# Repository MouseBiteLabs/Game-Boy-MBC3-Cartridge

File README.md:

# Game Boy MBC3 Cartridge

This is my design of a flashable MBC3-based cartridge for the Game Boy. The MBC3 mapper improves a lot over the MBC1, and includes a real-time clock for everyone's favorite battery-sucking game.... Mary Kate and Ashley Pocket Planner! Oh, and Pokemon.

This circuit board should cover most, if not all, MBC3 games. The features are as follows:

- Able to make games up to 2 MB in size, that use up to 256 Kbit of RAM
- Compatibility with all four of the popular Game Boy battery management ICs - MM1026, MM1134, BA6129, and BA6735
- The option to add battery backup to the cartridge *without* the need of the original battery management ICs
- Fully compatible with the <a href="https://www.gbxcart.com/">GBxCart RW</a> so you can transfer games and save files to and from the board
- 

All gerbers and source files can be found in this repo, as this project is fully open source. Technical documentation of the board can be found in the Technical folder.

## Important Things Before You Start

1) To use this board, you need to have an original Game Boy game that uses an MBC3 mapper chip. <a href="https://catskull.net/gb-rom-database/">You can find a list of games and their mappers here</a>. Use the search function. Please note the RAM is in bytes, not bits. Since SRAM in this repo is defined in bits, you need to convert by multiplying the number of bytes by 8.
2) You will need to remove the MBC3 from your donor cartridge for use on this board. This will require a hot air rework station or a hot plate. There's a list below of other parts you can re-use from the donor cartridge.
3) When soldering parts on, it's a good idea to put kapton tape or otherwise cover the bottom cartridge edge. You do not want to get solder on the cartridge contacts.
4) I am not responsible for any damage you do to your self or your property. Attempt this project at your own risk.
5) I do not guarantee design compatibility. You may encounter issues with certain games. There is also a chance I have made an error in the design or the BOM - if this is the case, I will do everything I can to address the problem as quickly as possible.
6) If you are using this board to make games other than for personal use, you must have permission from the originator to use and distribute any ROM images or other related material. You are responsible for making sure you adhere to any license requirements.

DO NOT use my circuit boards for profiting from stolen work - this especially includes homebrew content, ROM hacks, and using fan-made labels without permission from the originator. **Support original creators!**

## Board Characteristics and Order Information

The zipped folder contains all the gerber files for this board. The following options **must** be chosen when ordering boards for yourself.

- Thickness: 0.8mm
- Surface Finish: ENIG
- Gold Fingers: Yes, 30° chamfer

**Add this note to orders:** "The milling.gbr layer indicates where an unplated slot should be added to the board. Please add an unplated slot as indicated."

**I sell this blank circuit board on Etsy, so you don't have to buy a bunch of multiples if you don't want to.** (Click the banner!)

You can use the zipped folder at any board fabricator you like. You may also buy the board from PCBWay using this link (disclosure: I receive 10% of the sale value to go twoards future PCB orders of my own):

<a href="https://oshpark.com/shared_projects/6rPI4Bk8">The board is also listed on OSH Park as well.</a> **Be sure to get them in 0.8mm thickness if you order from here.**

## Required Equipment

The EEPROMs on the board needs to be programmed somehow. I recommend using the GBxCart, as mentioned. These boards are fully compatible with it, and it makes reflashing games extremely easy using <a href="https://github.com/lesserkuma/FlashGBX">lesserkuma's FlashGBX software</a>.

Alternatively, you can buy an EEPROM programmer with a TSOP adapter. The downside to this method is that you have to desolder the chip every time you want to program it. The <a href="https://flashcatusb.com/">FlashcatUSB</a> is one popular option in retro spaces.

## Battery Safety

When assembling a board, I recommend populating all the parts *except* the battery, and getting it to run initially without it. This is to make it easier to fix any solder connections that might need fixing, without having to worry about getting the battery hot. And if you need to rework anything near the battery after you've put it on the board, be safe and remove it before putting a hot soldering iron next to it.

And this should go without saying, but if you're assembling these boards with a hot plate or hot air, *do not* solder the battery on this way. You should use an iron, and keep heat off of the battery as much as possible. 

(Also check polarity!)

## Board Configurations

The board comes with five sets of jumper pads for solder bridges. SJ3, SJ5, and SJ6 require you to solder bridge the middle pad either to the left or right pads. SJ1 and SJ4 are configured by either leaving them alone or bridging them with solder. Here are the situations where you need to add solder bridges.

### Making Games Without SRAM or Battery (SJ1 and SJ4)

Solder bridge SJ1 and SJ4 if your game does not use any SRAM or battery. I don't believe there were ever any MBC3 games made *without* SRAM, but if you wanted to... remove it for some reason, you can.

### MBC3 Type Select (SJ3)

The MBC3 chip you use from the donor cartridge can be one of a few different types:

- If your MBC3 doesn't have a revision letter on it (it just says "MBC3" on it) then bridge the middle pad of SJ3 to the left. (You will also need to populate Q1!)
  - If you're using a revision-less MBC3, and are making a game that requires a battery, you should use a donor MM1026, MM1134, BA6129, or BA6735 battery management IC instead of the replacement TPS3613.
- If your MBC3 *does* have a revision letter, such as MBC3A or MBC3B, then bridge the middle pad of SJ3 to the right.

*[Images of MBC3 chips from <a href="https://gbhwdb.gekkio.fi/cartridges/mbc3.html">Game Boy Hardware Database</a>.]*

### RAM Size Selection (SJ5 and SJ6, or SW1)

These jumpers are located underneath the MBC3 chip, and labeled "64K" and "256K". Solder them to configure the amount of RAM your cart uses. You must configure these pads for every game you make, unless you do not need RAM. <a href="https://catskull.net/gb-rom-database/">You can find a list of games here with their respective RAM sizes.</a>

- If the game you're making uses 256 Kbit of RAM, then solder the middle pads of the two jumper sets to the right pads.
- If the game you're making uses 64 Kbit of RAM, then solder the middle pads of the two jumper sets to the left pads.
- SJ5 and SJ6 must be soldered in the same direction.
- The footprint of these selection pads should allow for a DPDT switch, part number CAS-220A1, to be placed on these pads instead of having to bridge the pads with solder.

Note that you can make games that only require 64 Kbit of RAM and still use a 256 Kbit SRAM chip. You still need to configure the jumpers to the 64 Kbit setting, though.

### Games Without a Real-Time Clock

If your game does *not* use the RTC function with the crystal X1, then you need to bridge the pads of Z1 (which is called C3 on v1.3 and earlier).

## Test Points and Final Checkout

On the back of the board are five test points. Here's where they are connected:

- TP1: SRAM supply voltage
- TP2: Battery voltage (after R1)
- TP3: Battery voltage (positive terminal of battery)
- TP4: Ground
- TP5: VCC input voltage

After you assemble your game, you should measure the current out of the battery. But first, you should program it with the GBxCart, or if you programmed the EEPROM separately, put it into a Game Boy and cycle power once. Then, flip the PCB upside down on a non-conductive surface (not your leg), and set your multimeter in DC millivolts (or volts). Put the positive probe on TP3 and the negative probe on TP2. If you used a 10kΩ for R1, as indicated in the BOM, you should read a voltage in the single or tens of millivolts for non-RTC games, or up to 40 mV for games using a real-time clock. If you have something much higher, especially voltages above 40mV, then you likely have an issue or short circuit on the board somewhere.

**Note: You need to power up the game at least once before battery currents will make sense - the battery management ICs can start up in an unknown state before applying main power to the board.**

To estimate battery life, see <a href="https://github.com/MouseBiteLabs/Game-Boy-MBC3-Cartridge/tree/main/Technical#estimating-battery-life">this section in the Technical Design Document</a>, or for more in-depth analysis, <a href="https://hackaday.io/project/11864-tritiled/log/72554-determining-maximum-runtime-176-to-202-years-cr2032">this Hackaday post</a>.

### Current Draw Measurements

The revision of MBC3 chip you are using will influence the current draw out of the battery when the game is off, and thus how long your battery life will last. Using the real-time clock function on the MBC3 will draw more current than if you do not.

For the test set up, I am replacing the battery with a regulated DC power supply set for 3 VDC for consistency, on a cart board with an MM1134 chip for U4, and brand new AS6C62256 SRAM. The "no RTC" measurements have Z1 (or C3) shorted, and the "with RTC" measurements have R2, C2, Z1, and X1 populated. I am using a Fluke 117 Multimeter in DC mV mode for measurements.

| Rev   | P/N      | Current draw (without RTC) | Battery Life Estimate (no RTC, CR2025) | Current draw (with RTC) | Battery Life Estimate (RTC, CR2025)  | Battery Life Estimate (RTC, CR2032) |
| ----- | -------- | -------------------------- | -------------------------------------- | ----------------------- | ------------------------------------ | ----------------------------------- |
| MBC3  | LR385364 |          0.2 uA            |               >50 years                |            1.8 uA       |               10 years               |            14 years                 |
| MBC3  | BU3631K  |          0.6 uA            |                31 years                |            1.6 uA       |               12 years               |            16 years                 |
| MBC3  | P-1      |          0.4 uA            |                47 years                |            3.8 uA       |               5 years                |             7 years                 |
| MBC3A | LR38536B |          0.2 uA            |               >50 years                |            1.5 uA       |               13 years               |            18 years                 |
| MBC3A | BU3632K  |          0.5 uA            |                37 years                |            1.5 uA       |               13 years               |            18 years                 |
| MBC3A | P-2      |          0.5 uA            |                37 years                |            3.9 uA       |               5 years                |            7 years                  |
| MBC3B | BU3634K  |          0.6 uA            |                31 years                |            1.5 uA       |               13 years               |            18 years                 |
| MBC3B | P-2      |          0.4 uA            |                47 years                |            3.7 uA       |               5 years                |            7 years                  |

*Note: The SRAM I used, AS6C62256, drew 0.05 uA by itself for these tests. Your current draw may vary depending on the SRAM you are using.*

### Why not FRAM?

This board is only suitable for using SRAM. One downside to SRAM, if you haven't figured it out yet, is that you need a battery to keep the SRAM powered on even when the game is turned off. So eventually the battery will die, and your save data is lost. Some people have used FRAM, or Ferroelectric RAM, to keep save data around even after the battery dies (specifically, the popular part that's used for FRAM carts is the FM18W08). But, using this FRAM chip has a handful of downsides, and the benefit of keeping save data after the battery dies *in my opinion* does not outweigh the cons, which are as follows:

1) Quality, new stock, 5V tolerant FRAM is expensive ($12+ per part).
2) Cheaper FRAM chips from eBay or Aliexpress are notoriously flaky (anecdotally, ~50% success rate).
3) FRAM memory access requires different chip select timing than SRAM, and the Game Boy expects SRAM, so it is not natively compatible with FRAM carts. The Gameboy Color specifically cannot (easily) be made to properly access FM18W08 chip. You *can* use an OR gate and add the CLK on the cart edge to try to achieve the necessary timing, but it only works (properly) for DMG/MGB/SGB, not the GBC. It usually *works* in practice for GBC, but it's technically a datasheet violation and can potentially cause issues in edge cases. <a href="https://github.com/Gekkio">(Thanks to gekkio for pointing this out!)</a>

Brand new SRAM chips are ~$3, and having the SRAM footprint also allows you to use SRAM from an original cart if desired. And other than the scenario where you are making a game with a real-time clock and are using an inefficient MBC3 variant (P-1 or P-2), you can easily get more than a decade of battery life. You're already assembling this cartridge; you can dump the save and replace the battery!

Note that this isn't to throw shade at any FRAM-based carts, but for me personally, it's more trouble than it's worth. If you just *need* FRAM, you can find other cart designs out there that have it, <a href="https://retrogamerepairshop.com/products/game-boy-2mb-32kb-fram-mbc3-with-rtc-flash-cartridge-by-hdr?variant=40144623927468">like this one!</a>

## Board Fitment

The shape of this board was originally meant to mimic original Game Boy circuit boards as closely as possible (v1.3 and earlier). Unfortunately, when placed in some aftermarket Game Boy cartridge shells (like those from Cloud Game Store), the circuit board has a lot of freedom to rotate around the main screw hole in the bottom-middle of the cartridge. This can cause misalignment when you put it in a Game Boy, which can cause a game to either not load properly (garbled Game Boy logo) or shut off the Game Boy because of a short circuit. This isn't *dangerous* or anything, just annoying.

In order to make the boards fit nicer in any kind of shell, for v1.4 I added extended tabs of circuit board material to the edges of the cartridges to keep it from rotating too much in shells, which was suggested to me by <a href="https://github.com/orangeglo">orangeglo</a>! (Thanks!)

If you're having trouble fitting the circuit board into a shell, because the tabs interfere with the cart edges, you can safely sand or trim them down as there is no copper within the tabs themselves. The only shell that appears to require any kind of trimming are Kitsch-Bent shells.

## Bill of Materials (BOM)

Your parts list will vary depending on the game you are trying to make, and what chips you have for the battery management (if any). **You cannot use both U4 and U5 - you must choose one or the other.** U4 comes from a donor cartridge, and U5 is a readily available aftermarket option.

Please carefully review the parts you need for the board you are trying to make. Do not add any parts to your build that don't appear in the column for the game you are making. This means you *cannot* populate every component on the board at the same time.

**NOTE: If you are *not* using the RTC function of the MBC3, you need to bridge the pads of Z1 (or C3) with solder.**

| Reference Designators | Value/Part Number              | Package          | Description        | No save carts | Save carts with U4 | Save carts without U4 | Source                                           |
| --------------------- | ------------------------------ | ---------------- | ------------------ | ------------- | ------------------ | --------------------- | ------------------------------------------------ |
| B1                    | CR2032, CR2025, CR2016         | CR2032           | Backup Battery     |               | x                  | x                     | [https://mou.sr/3SeAzfT](https://mou.sr/3SeAzfT) |
| C1                    | 0.1uF                          | 0603             | Capacitor (MLCC)   | x             | x                  | x                     | [https://mou.sr/3ENc15O](https://mou.sr/3ENc15O) |
| C2                    | 15pF                           | 0603             | Capacitor (MLCC)   |               | If using RTC       | If using RTC          | https://mou.sr/3PPorjO                           |
| Z1 (or C3)            | 15pF                           | 0603             | Capacitor (MLCC)   |               | If using RTC       | If using RTC          | https://mou.sr/3PPorjO                           |
| C4                    | 0.1uF                          | 0603             | Capacitor (MLCC)   |               | x                  |                       | [https://mou.sr/3ENc15O](https://mou.sr/3ENc15O) |
| C5                    | 0.1uF                          | 0603             | Capacitor (MLCC)   |               | x                  | x                     | [https://mou.sr/3ENc15O](https://mou.sr/3ENc15O) |
| C6                    | 10uF                           | 0603             | Capacitor (MLCC)   |               | x                  | x                     | [https://mou.sr/3mZtSkF](https://mou.sr/3mZtSkF) |
| C7                    | 0.1uF                          | 0603             | Capacitor (MLCC)   | x             | x                  | x                     | [https://mou.sr/3ENc15O](https://mou.sr/3ENc15O) |
| C8                    | 0.1uF                          | 0603             | Capacitor (MLCC)   |               |                    | x                     | [https://mou.sr/3ENc15O](https://mou.sr/3ENc15O) |
| Q1                    | 2N7002                         | SOT-23           | N-Channel FET      |               | If MBC3 no rev     | x                     | [https://mou.sr/3rgfh6J](https://mou.sr/3rgfh6J) |
| R1                    | 10k                            | 0603             | Resistor           |               | x                  | x                     | [https://mou.sr/3riR7IH](https://mou.sr/3riR7IH) |
| R2                    | 330k                           | 0603             | Resistor           |               | If using RTC       | If using RTC          | [https://mou.sr/3PZ2pvj](https://mou.sr/3PZ2pvj) |
| R8                    | 10k                            | 0603             | Resistor           | x             | x                  | x                     | https://mou.sr/3riR7IH                           |
| R9                    | 130k                           | 0603             | Resistor           |               |                    | x                     | [https://mou.sr/3MjXliy](https://mou.sr/3MjXliy) |
| R10                   | 49.9k                          | 0603             | Resistor           |               |                    | x                     | https://mou.sr/3Q3NRZO                           |
| U1                    | 29F016, 29F032, 29F033         | TSOP-48, TSOP-40 | Flash EEPROM       | x             | x                  | x                     | AliExpress or eBay                               |
| U2                    | MBC3                           | QFP-32           | MBC3 Mapper        | x             | x                  | x                     | Donor MBC3 Game Boy cartridge                    |
| U3                    | AS6C6264, AS6C62256            | SOP-28           | SRAM               |               | x                  | x                     | [https://mou.sr/450klcY](https://mou.sr/450klcY) |
| U4                    | MM1026, MM1134, BA6129, BA6735 | SOIC-8           | Battery Management |               | x                  |                       | Donor Game Boy cartridge                         |
| U5                    | TPS3613                        | MSOP-10          | Battery Management |               |                    | x                     | [https://mou.sr/45Ir2kh](https://mou.sr/45Ir2kh) |
| X1                    | 32.768 kHz                     | Radial           | Crystal Oscillator |               | If using RTC       | If using RTC          | https://mou.sr/3ZteKuy                           |

*Note that C9 - C11 footprints are only included on the board for strange edge cases that may require them sometime in the future; do not populate! See the technical design document for more information.*

### Usable Donor Cartridge Parts

You can use a few parts from the donor cart on the new board to save some money. Note that you will generally get better reliability with new parts as opposed to old ones. For example: I have seen failed RAM chips from donors in the past.

1) **C1/Z1, C2, R2, X1: RTC Components** - You can move over these parts if you're using the real-time clock function. The two capacitors are the same value, so they are interchangeable. On games that *don't* use the RTC, you can't move "Z1" over, because it's a resistor on those boards. Also be careful that on my board, the RTC capacitors are designated as "Z1" (or "C3") and "C2" - don't accidentally move the wrong capacitors over from the donor board to these spots!
2) **U2: MBC3** - This one is required
3) **U3: SRAM** - You can use this part *only if* the game you're making uses the same or less amount of RAM that the donor cartridge does
4) **U4: Battery Management IC** - Using this is probably preferred over the TPS3613 because it'll save you money and parts to put on

You could probably transfer over most of the 0.1uF capacitors but they're pretty cheap anyway, so I generally just recommend buying new resistors and capacitors.

### Capacitors C9 to C11

If you want to experiment with the capacitors C9 to C11, see this info below. **Be aware that adding these components in some of my tests actually ***stopped*** games from working, so again, assume that if you have a problem it lies elsewhere first, because it almost certainly does.**
- C9 is a capacitor connected nearby the SRAM's /WE pin to GND. These were populated on some cartridges, and I believe have a value of approximately 1 nF (0.001 uF) based on measurements from an MBC1 board that used it.
- C10 is a capacitor connected from the cart edge /RESET pin to GND. A spot for this capacitor was included on some MBC1 carts, but I cannot locate an instance of it actually being used when looking through the gbhwdb. It does not appear on *any* MBC3 boards. I don't actually know what value this capacitor would need to be, so I am guessing 1 nF.
- C11 is a capacitor that I have added that was not used on any original Game Boy board. It connects to the SRAM's /CE pin, bypassing to GND. I have added this in the event incompatibilities arise with newer SRAM chips that have much faster speeds than older SRAM chips. This was a problem I encountered on some of my NES cartridges, so this is here just in case, but I have not found an instance where it's required.

## Things to Remember

- The footprint for the EEPROM is specifically for 29F016 - it has 48 pins. However, 29F032 and 29F033 are only 40 pin devices. They still work fine on the board though - place them in the center of the footprint, and leave the outer two pins on each corner empty
- The 29F016, 29F032, and 29F033 have been known to occasionally be defective upon arrival. They're either used, or new old stock, and usually only available from AliExpress.
- The footprint for the battery can fit a CR2032, CR2025, or CR2016 with solder tabs. The only difference is the mAh capacity (larger number = longer life). If you get Panasonic tabbed batteries, you may have to trim the battery tabs to make them fit on the footprint.
  - For untabbed coin cells, you can find battery retainer adapters online, <a href="https://retrogamerepairshop.com/products/hdr-game-boy-game-battery-retainer?variant=40511013290156">like this one,</a> but only for board revision v1.4. It will not fit on earlier revisions.
- For battery management, use either U4 *or* U5 and supporting components. **Do not** use U4 and U5 simultaneously on one board. They will interfere with each other.
- Generally, ROM sizes are conveyed in terms of kilo**bytes** and mega**bytes** (KB, MB). RAM size is usually conveyed in terms of kilo**bits** or mega**bits** (Kbit, Mbit). You can convert Kbit and Mbit to KB and MB by dividing Kbit or Mbit by 8. For example, 256 Kbit = 32 KB.
- You only need to provide ROM and RAM chips that have at least *or greater* the size of the game you are trying to make. That means you can use a 256 Kbit SRAM chip for a game that only requires 64 Kbit of RAM!

## Labels

If you want a Bucket Mouse branded label for your cartridge, look no further than <a href="https://krizdingus.com/mousebitelabs/">krizdingus's designs</a>. Special thanks to Kris for designing these, they look awesome! (If you are going to order/print these, use the high-res images hosted on his website, and *keep the labels for personal or non-commercial use only.*)

## Revision History

### v1.4
- Changed "C3" to "Z1"
- Reduced cart edge by 0.1 mm for better fitment
- Adjusted battery placement to support more battery holders
- Added tabs on the board edges to allow the circuit board to fit better in aftermarket cartridge shells

### v1.3
- Extended cart edge down by 0.25 mm for better fitment
- Added OSHW logo and "SUPPORT ORIGINAL CREATORS!"

### v1.2
- Replace non-donor battery management circuitry with a TPS3613-based circuit for smaller BOM and easier routing

### v1.1
- Moved all parts on the top down to allow for compatibility with DMG-style shells
- Rotated battery for more space
- Widen SRAM footprint for easier soldering
- Renamed some reference designators for consistency between designs
- Changed silkscreen for clarity

### v1.0
- Prototype revision

## Resources and Acknowledgements

- <a href="http://www.devrs.com/gb/files/hardware.html">Jeff Frohwein's GameBoy Tech Page</a>
- <a href="https://gbhwdb.gekkio.fi/">Game Boy Hardware Database</a>
- <a href="https://catskull.net/gb-rom-database/">Nintendo Gameboy Game List</a>
- <a href="https://www.gbxcart.com/">insideGadgets discord server for GBxCart RW compatibility requirements</a>
- <a href="https://github.com/lesserkuma/FlashGBX">Lesserkuma's FlashGBX software</a>
- <a href="https://www.alldatasheet.com/datasheet-pdf/pdf/99104/MITSUBISHI/MM1026.html">System Reset IC Datasheet</a>
- <a href="https://www.ti.com/lit/ds/symlink/tps3613-01.pdf?HQS=dis-mous-null-mousermode-dsf-pf-null-wwe&ts=1698238885366&ref_url=https%253A%252F%252Feu.mouser.com%252F">TPS3613 Datasheet</a>
- Board outline modified from <a href="https://tinkerer.us/projects/homebrew-gameboy-cartridge.html">Dillon Nichols's Homebrew Gameboy Cartridge project</a>
- Thanks to <a href="https://github.com/orangeglo">orangeglo</a> for his suggestion of adding spacers around the board edge for better fitment in aftermarket cartridges
- Some components from <a href="https://github.com/adafruit/Adafruit-Eagle-Library">Adafruit's Eagle parts library</a>
- Some components from <a href="https://www.snapeda.com/">SnapMagic</a>
- Thank you to <a href="https://github.com/Gekkio">gekkio</a> for their deep Game Boy knowledge resources, and for collaboration in demystifying some of the design choices on Game Boy cartridges
- Thanks to the awesome members of the <a href="https://moddedgameboy.club/">Modded Gameboy Club</a> for their feedback and support during the entire project development

## License

<br />This work is licensed under a <a rel="license" href="http://creativecommons.org/licenses/by-sa/4.0/">Creative Commons Attribution-ShareAlike 4.0 International License</a>. You are able to copy and redistribute the material in any medium or format, as well as remix, transform, or build upon the material for any purpose (even commercial) - but you **must** give appropriate credit, provide a link to the license, and indicate if any changes were made.

©MouseBiteLabs 2023

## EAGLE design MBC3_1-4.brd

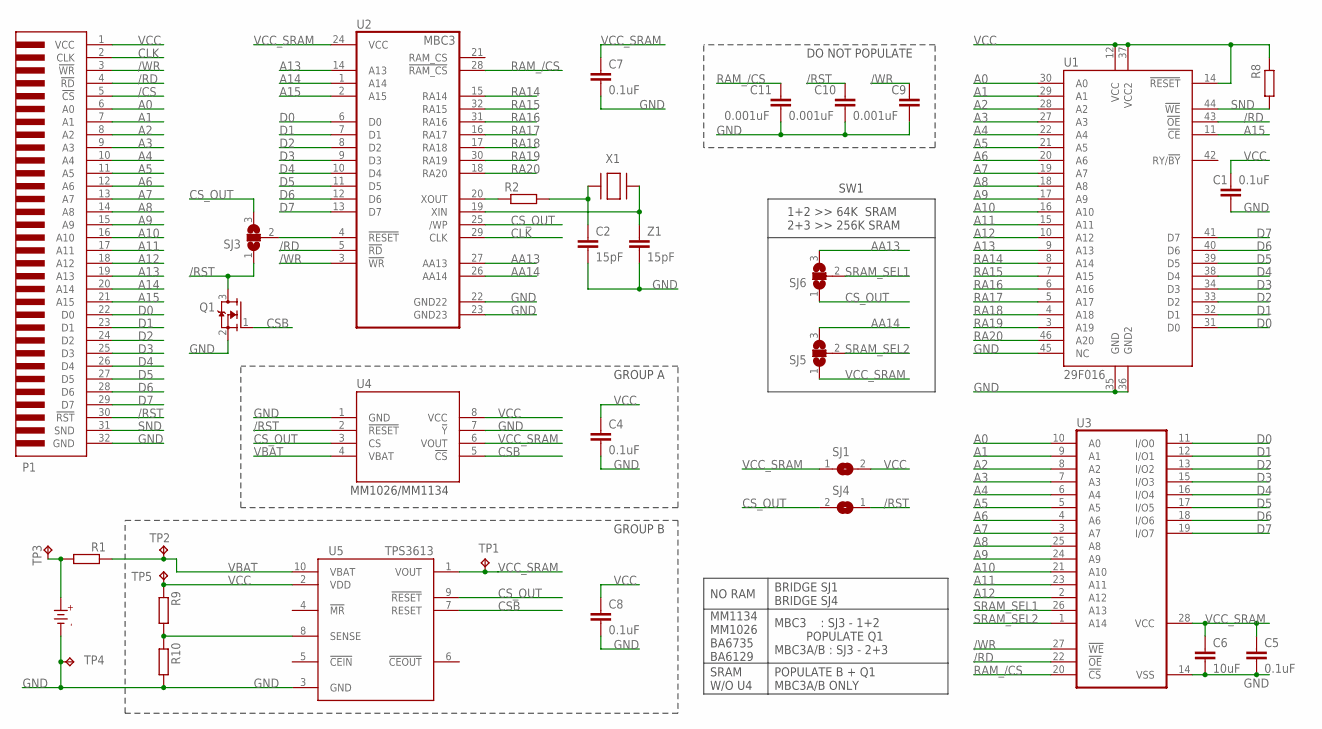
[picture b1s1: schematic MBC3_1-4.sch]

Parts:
B1: CR2025
C1, C4, C5, C7, C8: 0.1uF; C0603
C2: 15pF; C0603
C6: 10uF; C0603
C9, C10, C11: 0.001uF; C0603
P1: GBC_CARTTAB; GBC_CART_TABBED
Q1: 2N7002; SOT23
R1, R2, R8, R9, R10: RR0603; R0603
SJ1, SJ4: SJ
SJ3, SJ5, SJ6: SJ2W; SJ_2
TP1, TP2, TP3, TP4, TP5: TPB1,27; B1,27
U1: 29F016; TSOP-48
U2: MBC3; QFP-32
U3: 62256_SRAM; SOP-28L
U4: MM1134; SOIC-8
U5: TPS3613; MSOP-10
X1: XTAL-3.2X1.5; XTAL3215
Z1: 15pF; C0603

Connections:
/CS: P1.5 (!CS)
/RD: P1.4 (!RD), U1.43 (!OE), U2.5 (!RD), U3.22 (!OE)
/RST: C10.1, P1.30 (!RST), Q1.3 (D), SJ3.1, SJ4.1, U4.2 (!RESET)
/WR: C9.1, P1.3 (!WR), U2.3 (!WR), U3.27 (!WE)
A0: P1.6 (A0), U1.30 (A0), U3.10 (A0)
A1: P1.7 (A1), U1.29 (A1), U3.9 (A1)
A2: P1.8 (A2), U1.28 (A2), U3.8 (A2)
A3: P1.9 (A3), U1.27 (A3), U3.7 (A3)
A4: P1.10 (A4), U1.22 (A4), U3.6 (A4)
A5: P1.11 (A5), U1.21 (A5), U3.5 (A5)
A6: P1.12 (A6), U1.20 (A6), U3.4 (A6)
A7: P1.13 (A7), U1.19 (A7), U3.3 (A7)
A8: P1.14 (A8), U1.18 (A8), U3.25 (A8)
A9: P1.15 (A9), U1.17 (A9), U3.24 (A9)
A10: P1.16 (A10), U1.16 (A10), U3.21 (A10)
A11: P1.17 (A11), U1.15 (A11), U3.23 (A11)
A12: P1.18 (A12), U1.10 (A12), U3.2 (A12)
A13: P1.19 (A13), U1.9 (A13), U2.14 (A13)
A14: P1.20 (A14), U2.1 (A14)
A15: P1.21 (A15), U1.11 (!CE), U2.2 (A15)
AA13: SJ6.3, U2.27 (AA13)
AA14: SJ5.3, U2.26 (AA14)
CLK: P1.2 (CLK), U2.29 (CLK)
CSB: Q1.1 (G), U4.5 (!CS), U5.7 (RESET)
CS_OUT: SJ3.3, SJ4.2, SJ6.1, U2.25 (/WP), U4.3 (CS), U5.9 (!RESET)
D0: P1.22 (D0), U1.31 (D0), U2.6 (D0), U3.11 (I/O0)
D1: P1.23 (D1), U1.32 (D1), U2.7 (D1), U3.12 (I/O1)
D2: P1.24 (D2), U1.33 (D2), U2.8 (D2), U3.13 (I/O2)
D3: P1.25 (D3), U1.34 (D3), U2.9 (D3), U3.15 (I/O3)
D4: P1.26 (D4), U1.38 (D4), U2.10 (D4), U3.16 (I/O4)
D5: P1.27 (D5), U1.39 (D5), U2.11 (D5), U3.17 (I/O5)
D6: P1.28 (D6), U1.40 (D6), U2.12 (D6), U3.18 (I/O6)
D7: P1.29 (D7), U1.41 (D7), U2.13 (D7), U3.19 (I/O7)
GND: B1.-, C1.2, C2.2, C4.2, C5.2, C6.2, C7.2, C8.2, C9.2, C10.2, C11.2, P1.32 (GND), Q1.2 (S), R10.2, TP4.TP, U1.35 (GND), U1.36 (GND2), U1.45 (NC), U2.22 (GND22), U2.23 (GND23), U3.14 (VSS), U4.1 (GND), U4.7 (!Y), U5.3 (GND), Z1.2
unnamed: SJ3.2, U2.4 (!RESET)
unnamed: B1.+, R1.2, TP3.TP
unnamed: R2.1, U2.20 (XOUT)
unnamed: C2.1, R2.2, X1.P$2
unnamed: U2.19 (XIN), X1.P$1, Z1.1
unnamed: R9.2, R10.1, U5.8 (SENSE)
RA14: U1.8 (A14), U2.15 (RA14)
RA15: U1.7 (A15), U2.32 (RA15)
RA16: U1.6 (A16), U2.31 (RA16)
RA17: U1.5 (A17), U2.16 (RA17)
RA18: U1.4 (A18), U2.17 (RA18)
RA19: U1.3 (A19), U2.30 (RA19)
RA20: U1.46 (A20), U2.18 (RA20)
RAM_/CS: C11.1, U2.28 (!RAM_CS), U3.20 (!CS)
SND: P1.31 (SND), R8.2, U1.44 (!WE)
SRAM_SEL1: SJ6.2, U3.26 (A13)
SRAM_SEL2: SJ5.2, U3.1 (A14)
VBAT: R1.1, TP2.TP, U4.4 (VBAT), U5.10 (VBAT)
VCC: C1.1, C4.1, C8.1, P1.1 (VCC), R8.1, R9.1, SJ1.2, TP5.TP, U1.12 (VCC), U1.14 (!RESET), U1.37 (VCC2), U4.8 (VCC), U5.2 (VDD)
VCC_SRAM: C5.1, C6.1, C7.1, SJ1.1, SJ5.1, TP1.TP, U2.24 (VCC), U3.28 (VCC), U4.6 (VOUT), U5.1 (VOUT)

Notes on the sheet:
GROUP B
NO RAM
BRIDGE SJ1 BRIDGE SJ4
MM1134 MM1026 BA6735 BA6129
MBC3 : SJ3 - 1+2 POPULATE Q1 MBC3A/B : SJ3 - 2+3
SRAM W/O U4
POPULATE B + Q1 MBC3A/B ONLY
1+2 >> 64K SRAM 2+3 >> 256K SRAM
MM1026/MM1134
GROUP A
DO NOT POPULATE
SW1

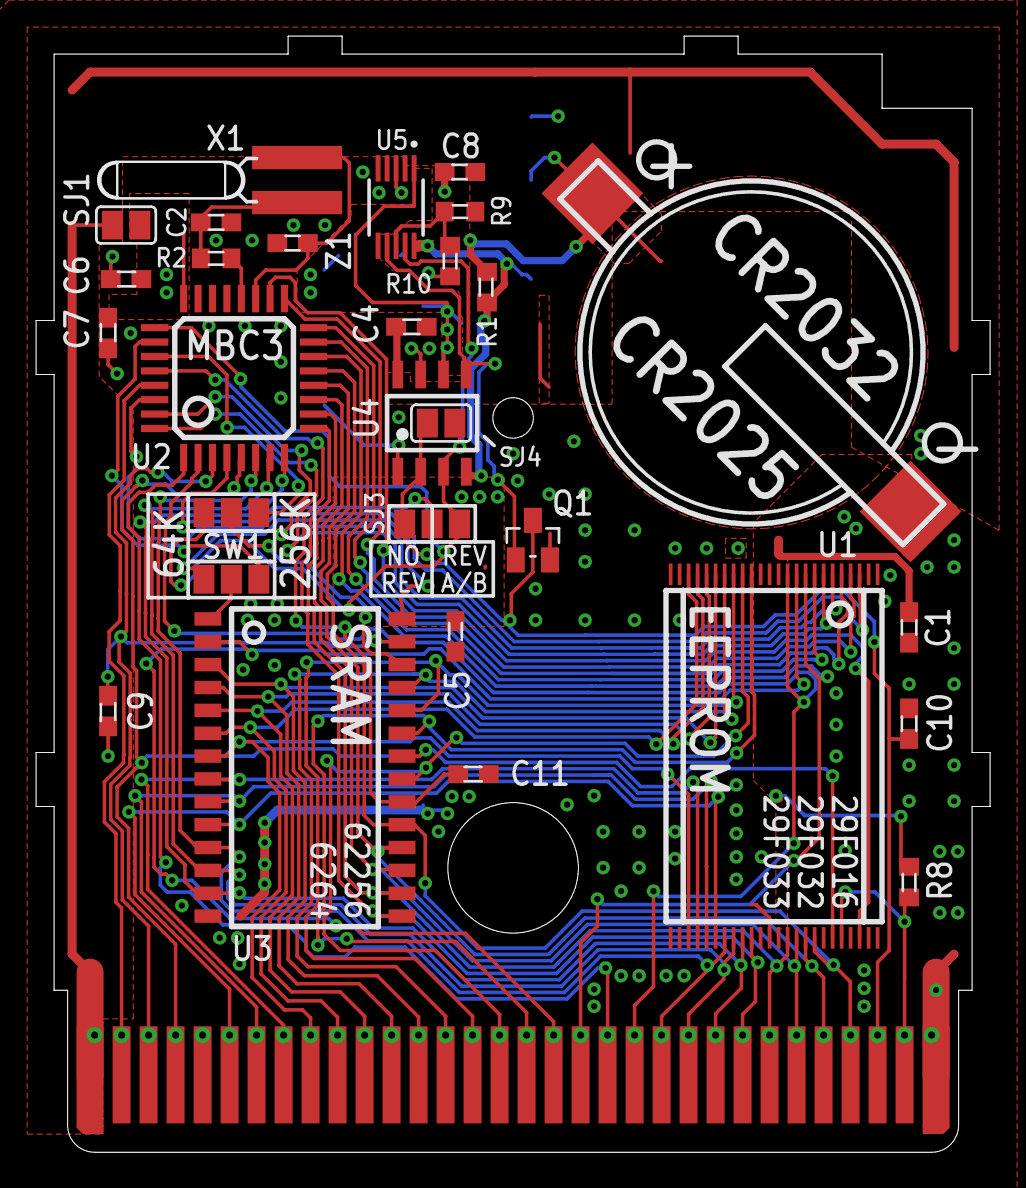
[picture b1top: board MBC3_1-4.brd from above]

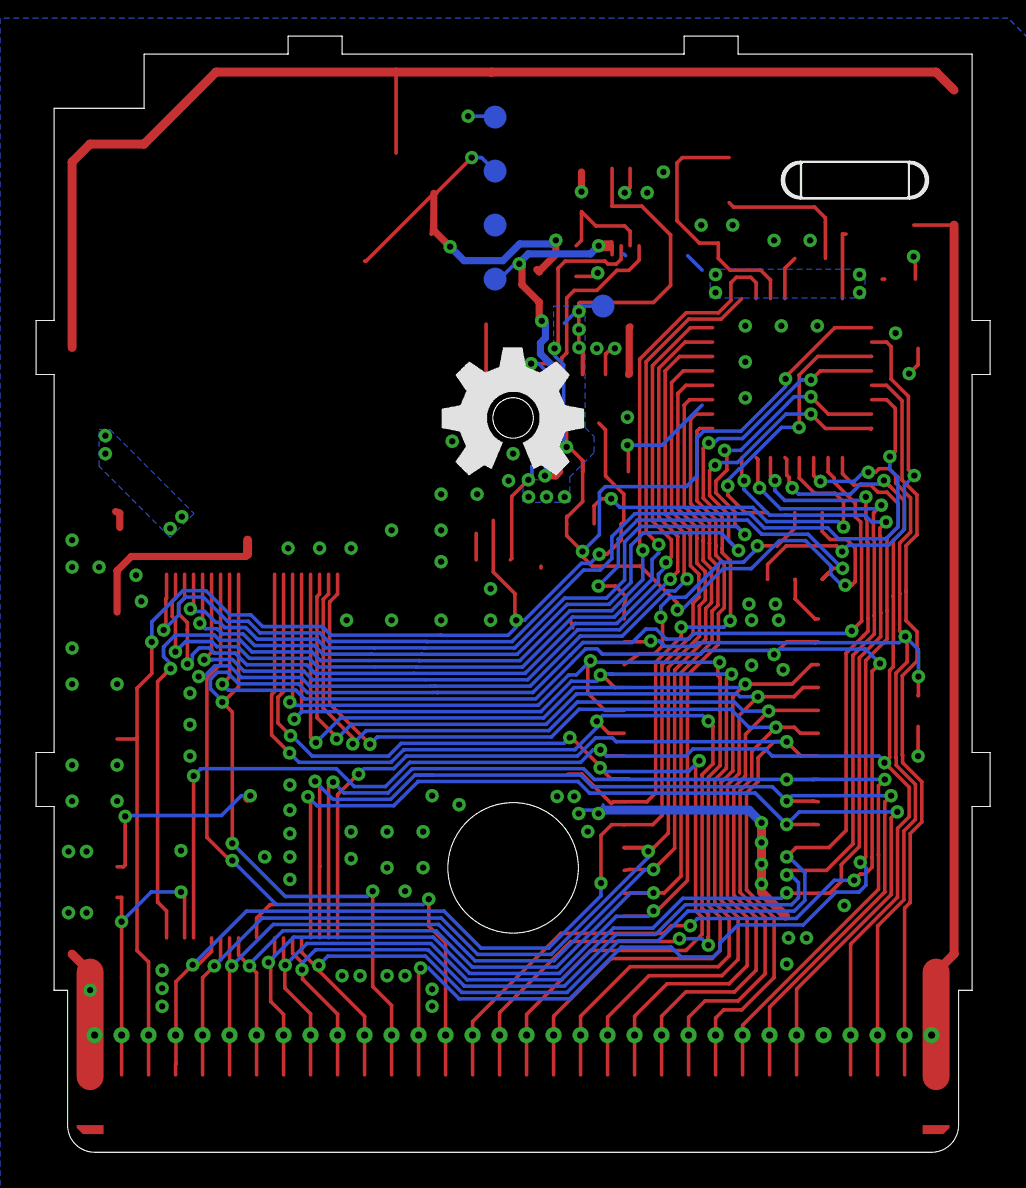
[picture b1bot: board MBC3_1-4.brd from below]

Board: 2 copper layers, 53.0 x 62.0 mm, 35 parts (5 on the bottom side), 53 nets.

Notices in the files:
README.md:
This work is licensed under a Creative Commons Attribution-ShareAlike 4.0 International License. You are able to copy and redistribute the material in any medium or format, as well as remix, transform, or build upon the material for any purpose (even commercial) - but you **must** give appropriate credit, provide a link t
©MouseBiteLabs 2023
